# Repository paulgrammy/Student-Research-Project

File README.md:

# Student-Research-Project-
Bluetooth signal receiver with filter stage and AUX/Speaker output.

UseCase description: 

This project seeks to help students more easily understand the effects of filters on electric signals by using sound. Since Music and/or audio is composed of frequencies across a spectrum (20Hz to 20kHz), one can hear what an Low/High Pass filter would do when fed audio signals. In my Student-Research project work, I try to design a PCB that shall overline this use case.

The PCB shall process analog converted audio signal coming from a Bluetooth-capable ESP32 board. The user shall connect the board at the input and output of any given filter and shall have the option to hear the filtered and unfiltered audio signals coming out with minimal noise and distortion.

Used platforms and ICs:

- ESP32 FireBeetle board:
    https://wiki.dfrobot.com/FireBeetle_Board_ESP32_E_SKU_DFR0654
- PCM5102 DAC:
    https://www.ti.com/product/PCM5102
- MCP6001 OPAMPS:
    https://ww1.microchip.com/downloads/en/DeviceDoc/MCP6001-1R-1U-2-4-1-MHz-Low-Power-Op-Amp-DS20001733L.pdf
- TPA711 Power AMP:
    https://www.ti.com/product/TPA711

Potential software solutions for the BluetoothRx interface:

https://github.com/pschatzmann/ESP32-A2DP

https://github.com/YetAnotherElectronicsChannel/ESP32_Bluetooth_Audio_Receiver

Books and Papers:

https://web.mit.edu/6.101/www/reference/op_amps_everyone.pdf

End result:

Conclusions: 
The board works with minimal distortion up to the OpAmps single supply limits, offering almost no phase lag.
Some layout optimizations can be carried out to lower the noise floor and make implementation in the labs easier.

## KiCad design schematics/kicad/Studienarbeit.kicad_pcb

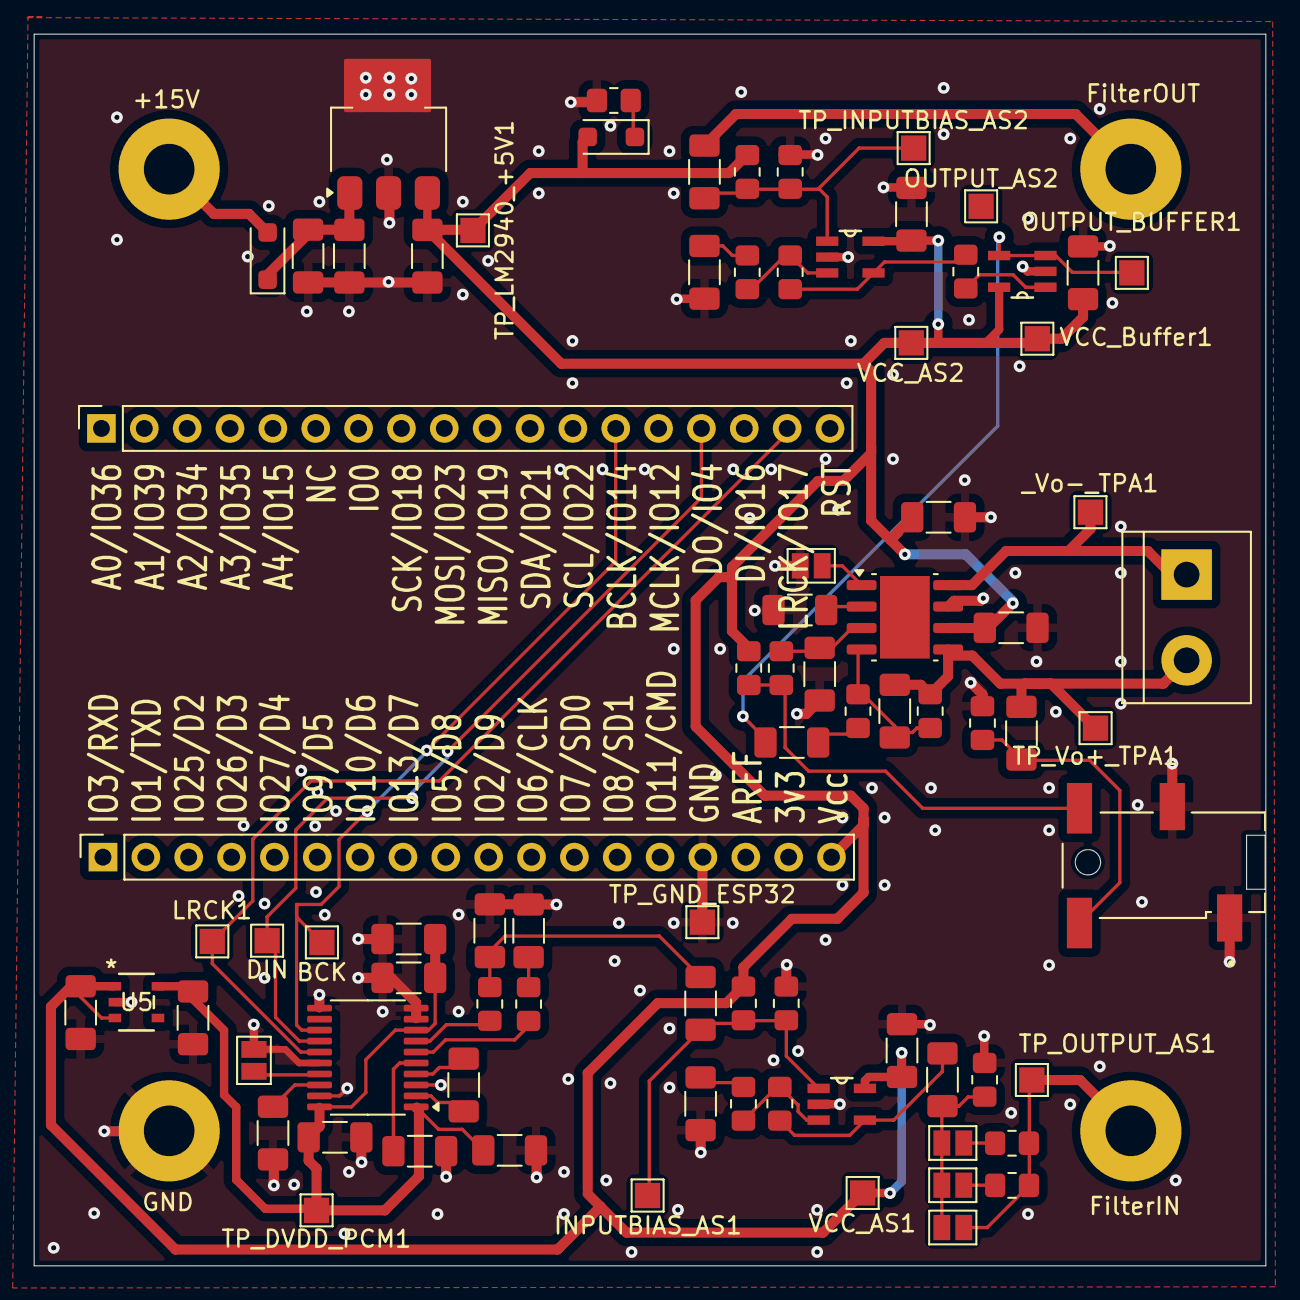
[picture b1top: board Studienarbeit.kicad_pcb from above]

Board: 2 copper layers, 73.0 x 73.0 mm, 87 parts (0 on the bottom side), 42 nets.

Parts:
BCK: TestPoint; TestPoint_Pad_1.5x1.5mm
C1_APS_PCM5102: 10uF; C_1206_3216Metric_Pad1.33x1.80mm_HandSolder
C1_CPPS_PCM1, C1_DPS_PCM1, C2_APS_PCM5102, C2_DPS_PCM1: 0.1uF; C_1206_3216Metric_Pad1.33x1.80mm_HandSolder
C2_CPPS_PCM1: 2.2uF; C_1206_3216Metric_Pad1.33x1.80mm_HandSolder
CA_PCM5102: 2.2uF; C_1206_3216Metric_Pad1.33x1.80mm_HandSolder
CB_TPA1: 2.2uF; C_1206_3216Metric_Pad1.33x1.80mm_HandSolder
CF_TPA711: 5pF; C_1206_3216Metric_Pad1.33x1.80mm_HandSolder
CG1_PCM5102, CG2_PCM5102: 2.2nF; C_1206_3216Metric_Pad1.33x1.80mm_HandSolder
CI_TPA711: 0.47uF; C_1206_3216Metric_Pad1.33x1.80mm_HandSolder
C_COUPLING_AMPSTAGE1: 10uF; C_1206_3216Metric_Pad1.33x1.80mm_HandSolder
C_COUPLING_AMPSTAGE2, C_COUPLING_AMPSTAGE3, C_COUPLING_AMPSTAGE4: 10nF; C_1206_3216Metric_Pad1.33x1.80mm_HandSolder
C_GND_AMPSTAGE1, C_GND_AMPSTAGE2, C_GND_AMPSTAGE3: 10uF; C_1206_3216Metric_Pad1.33x1.80mm_HandSolder
C_INPUT_LDO1: 0.47uF; C_1206_3216Metric_Pad1.33x1.80mm_HandSolder
C_INPUT_RT1: 22uF; C_1206_3216Metric_Pad1.33x1.80mm_HandSolder
C_INPUT_RT9080: 1uF; C_1206_3216Metric_Pad1.33x1.80mm_HandSolder
C_INPUT_TPA1, C_INPUT_TPA3: 10uF; C_1206_3216Metric_Pad1.33x1.80mm_HandSolder
C_INPUT_TPA2: 100nF; C_1206_3216Metric_Pad1.33x1.80mm_HandSolder
C_IN_+15V_1: 10uF; C_1206_3216Metric_Pad1.33x1.80mm_HandSolder
C_IN_AMPSTAGE1: 10uF; C_1206_3216Metric_Pad1.33x1.80mm_HandSolder
C_OUTPUT_LDO1: 22uF; C_1206_3216Metric_Pad1.33x1.80mm_HandSolder
C_SE/BTL_TPA1: 0.1uF; C_1206_3216Metric_Pad1.33x1.80mm_HandSolder
D1: D_Schottky; D_SOD-123F
D2: 1N4148; D_SOD-123F
DEBUG1: 0; R_0805_2012Metric_Pad1.20x1.40mm_HandSolder
DIN: TestPoint; TestPoint_Pad_1.5x1.5mm
INPUTBIAS_AS1: TestPoint; TestPoint_Pad_1.5x1.5mm
J2, J3: Conn_01x18; PinSocket_1x18_P2.54mm_Vertical
J4, J5, J6, J7: Conn_01x01_Pin; FestoBoard_Drill_Hole
J9: SJ2-35853B-SMT-TR; CUI_SJ2-35853B-SMT-TR
JP1, JP2, JP3, JP4, JP5: Jumper_2_Open; SolderJumper-2_P1.3mm_Open_Pad1.0x1.5mm
LRCK1: TestPoint; TestPoint_Pad_1.5x1.5mm
LS1: Speaker; TerminalBlock_bornier-2_P5.08mm
OUTPUT_AS2: TestPoint; TestPoint_Pad_1.5x1.5mm
OUTPUT_BUFFER1: TestPoint; TestPoint_Pad_1.5x1.5mm
R1, R2, R3, R4: 10K; R_0805_2012Metric_Pad1.20x1.40mm_HandSolder
R11: 1K; R_0805_2012Metric_Pad1.20x1.40mm_HandSolder
R12, R13: 100K; R_0805_2012Metric_Pad1.20x1.40mm_HandSolder
RF1, RF2: 5K; R_0805_2012Metric_Pad1.20x1.40mm_HandSolder
RF_TPA711: 50k; R_0805_2012Metric_Pad1.20x1.40mm_HandSolder
RG1: 100k; R_0805_2012Metric_Pad1.20x1.40mm_HandSolder
RG2: 100K; R_0805_2012Metric_Pad1.20x1.40mm_HandSolder
RI_TPA711: 10K; R_0805_2012Metric_Pad1.20x1.40mm_HandSolder
ROUTDACL1: 470; R_0805_2012Metric_Pad1.20x1.40mm_HandSolder
ROUTDACR1: 470; R_0805_2012Metric_Pad1.20x1.40mm_HandSolder
R_COUPLING_AMPSTAGE1: 100K; R_0805_2012Metric_Pad1.20x1.40mm_HandSolder
R_COUPLING_AMPSTAGE2: 10K; R_0805_2012Metric_Pad1.20x1.40mm_HandSolder
R_COUPLING_AMPSTAGE3: 1K; R_0805_2012Metric_Pad1.20x1.40mm_HandSolder
STATUS_LED1: 330; R_0805_2012Metric_Pad1.20x1.40mm_HandSolder
TP_DVDD_PCM1: TestPoint; TestPoint_Pad_1.5x1.5mm
TP_GND_ESP32: TestPoint; TestPoint_Pad_1.5x1.5mm
TP_INPUTBIAS_AS2: TestPoint; TestPoint_Pad_1.5x1.5mm
TP_LM2940_+5V1: TestPoint; TestPoint_Pad_1.5x1.5mm
TP_OUTPUT_AS1: TestPoint; TestPoint_Pad_1.5x1.5mm
TP_Vo+_TPA1: TestPoint; TestPoint_Pad_1.5x1.5mm
U1, U3, U4: MCP6001-OT; SOT95P270X145-5N
U2: PCM5102; TSSOP-20_4.4x6.5mm_P0.65mm
U5: RT9080-33GJ5; TSOT-23-5_RIT-L
U6: TPA711; Texas_R-PDSO-G8_EP2.95x4.9mm_Mask2.4x3.1mm
U7: LM2940CT-5.0; SOT-223
VCC_AS1, VCC_AS2: TestPoint; TestPoint_Pad_1.5x1.5mm
VCC_Buffer1: TestPoint; TestPoint_Pad_1.5x1.5mm
_Vo-_TPA1: TestPoint; TestPoint_Pad_1.5x1.5mm

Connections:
+3v3: C1_APS_PCM5102.1, C1_CPPS_PCM1.2, C1_DPS_PCM1.2, C2_APS_PCM5102.2, C_INPUT_RT1.2, TP_DVDD_PCM1.1, U2.1 (CPVDD), U2.8 (AVDD), U2.20 (DVDD), U5.5 (VOUT)
+5V: C_COUPLING_AMPSTAGE2.2, C_COUPLING_AMPSTAGE3.2, C_COUPLING_AMPSTAGE4.2, C_INPUT_RT9080.2, C_INPUT_TPA1.1, C_INPUT_TPA2.1, C_OUTPUT_LDO1.2, D2.2 (A), J2.18, R1.2, R3.2, R12.2, TP_LM2940_+5V1.1, U1.5 (V+), U3.5 (V+), U4.5 (V+), U5.1 (VIN), U5.3 (EN), U6.6 (V_{DD}), U7.3 (OUT), VCC_AS1.1, VCC_AS2.1, VCC_Buffer1.1
+15V: D1.2 (A), J5.1
/BCK: BCK.1, J3.13, U2.13 (BCK)
/BUFFEROUT: CI_TPA711.2, OUTPUT_BUFFER1.1, U3.3 (-), U3.4
/DIN: DIN.1, J3.15, U2.14 (DIN)
/Filter_IN: J7.1, JP3.2 (B), R_COUPLING_AMPSTAGE2.1, R_COUPLING_AMPSTAGE3.1, TP_OUTPUT_AS1.1
/Filter_OUT: C_IN_AMPSTAGE1.1, J6.1
/IN: CF_TPA711.1, RF_TPA711.2, RI_TPA711.2, U6.4 (IN)
/LDOO: C2_DPS_PCM1.1, U2.18 (LDOO)
/LRCK: J3.17, LRCK1.1, U2.15 (LRCK)
/OUTDACL: CG1_PCM5102.1, ROUTDACL1.2
/OUTDACR: CG2_PCM5102.1, C_GND_AMPSTAGE3.1, ROUTDACR1.2
/SE/~BTL_SWITCH: J9.10, R12.1, R13.1
/VNEG: C2_CPPS_PCM1.2, U2.5 (VNEG)
/Vo+: CF_TPA711.2, C_INPUT_TPA3.1, LS1.2, RF_TPA711.1, TP_Vo+_TPA1.1, U6.5 (V_{O+})
/Vo-: LS1.1, U6.8 (V_{O-}), _Vo-_TPA1.1
GND: C1_APS_PCM5102.2, C1_CPPS_PCM1.1, C1_DPS_PCM1.1, C2_APS_PCM5102.1, C2_CPPS_PCM1.1, C2_DPS_PCM1.2, CB_TPA1.2, CG1_PCM5102.2, CG2_PCM5102.2, C_COUPLING_AMPSTAGE2.1, C_COUPLING_AMPSTAGE3.1, C_COUPLING_AMPSTAGE4.1, C_GND_AMPSTAGE1.1, C_GND_AMPSTAGE2.1, C_INPUT_LDO1.1, C_INPUT_RT1.1, C_INPUT_RT9080.1, C_INPUT_TPA1.2, C_INPUT_TPA2.2, C_IN_+15V_1.2, C_OUTPUT_LDO1.1, C_SE/BTL_TPA1.2, J2.15, J4.1, J9.1, J9.3, JP4.1 (A), JP5.1 (A), R2.2, R4.2, R11.2, R_COUPLING_AMPSTAGE1.1, STATUS_LED1.1, TP_GND_ESP32.1, U1.2 (V-), U2.3 (CPGND), U2.9 (AGND), U2.10 (DEMP), U2.11 (FLT), U2.16 (FMT), U2.19 (DGND), U3.2 (V-), U4.2 (V-), U5.2 (GND), U6.7 (GND), U7.2 (GND), U7.4 (GND)
unnamed: CI_TPA711.1, RI_TPA711.1
unnamed: C_COUPLING_AMPSTAGE1.2, RF1.2, U4.4
unnamed: C_GND_AMPSTAGE1.2, RG1.1
unnamed: C_GND_AMPSTAGE2.2, RG2.1
unnamed: C_INPUT_TPA3.2, J9.2, R11.1
unnamed: C_INPUT_LDO1.2, C_IN_+15V_1.1, D1.1 (K), U7.1 (IN)
unnamed: D2.1 (K), STATUS_LED1.2
unnamed: DEBUG1.1, RF2.2, U1.4
unnamed: C_COUPLING_AMPSTAGE1.1, JP1.1 (A), JP2.1 (A), JP3.1 (A), R_COUPLING_AMPSTAGE1.2
unnamed: JP1.2 (B), R_COUPLING_AMPSTAGE2.2
unnamed: JP2.2 (B), R_COUPLING_AMPSTAGE3.2
unnamed: JP4.2 (B), U2.17 (XSMT)
unnamed: JP5.2 (B), U6.1 (SHUTDOWN)
unnamed: C_IN_AMPSTAGE1.2, R3.1, R4.1, TP_INPUTBIAS_AS2.1, U1.1 (+)
unnamed: RF2.1, RG2.2, U1.3 (-)
unnamed: CA_PCM5102.2, U2.4 (CAPM)
unnamed: CA_PCM5102.1, U2.2 (CAPP)
unnamed: ROUTDACL1.1, U2.6 (OUTL)
unnamed: ROUTDACR1.1, U2.7 (OUTR)
unnamed: DEBUG1.2, U3.1 (+)
unnamed: C_GND_AMPSTAGE3.2, INPUTBIAS_AS1.1, R1.1, R2.1, U4.1 (+)
unnamed: RF1.1, RG1.2, U4.3 (-)
unnamed: CB_TPA1.1, U6.2 (BYPASS)
unnamed: C_SE/BTL_TPA1.1, R13.2, U6.3 (SE/~BTL)

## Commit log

2024-05-15 Created first draft of block diagram.
2024-10-09 Imported LTSpice base schematic.
2024-10-09 Imported KiCAD schematics.
2024-10-09 Added Field-Notes for easy report structuring.
2024-10-09 Added notes for potential DAC PCB design.
2024-10-18 Updated LTSpice schematics.
2024-10-18 Updated Field Notes.
2024-10-18 LTSpice: Added AC-Coupling caps at output of first amp stage.
2024-10-18 KiCad: rewired PCM5120 I/O pins and dimentioned Rs and Cs
2024-10-18 KiCad: Rewired the TPA711 I/Os and dimentioned Rs and Cs
2024-10-18 KiCad: Grafics.
2024-10-18 KiCad: Added links to IC schematics.
2024-10-18 KiCad: Fixed a few ERC errors.
2024-10-18 KiCad: Dimentioned Cs.
2024-10-18 Added footprint folder for imported footprints.
2024-10-18 Added ESP32 Footprint.
2024-10-18 KiCad: Draft of PCB.
2024-10-20 KiCad: Added an LDO for stable supply voltage.
2024-10-20 LTSpice: Printed plots for report.
2024-10-20 Updated printed images.
2024-10-20 KiCad: Added test points in the schematic.
2024-10-22 Replace ESP32 Schematic with header pins.
2024-10-22 Updated schematic.
2024-10-24 Updated PCB.
2024-10-24 Added software folder.
2024-10-29 Updated the pcb schematic.
2024-10-29 Removed FIeld Notes.
2024-10-29 LTSpice: added jumper resistors for gain control.
2024-10-29 KiCad: Added jumper wires and resistors for gain control.
2024-10-29 KiCad: rerouted the jumpers.
2024-10-29 Random.
2024-11-04 Updated PCB based on feedback (1).
2024-11-07 Updated the PCB with prof feedback.
2024-11-07 Updated the parts list.
2024-11-07 Added screenshots of simulation.
2024-11-13 Added schematic screenshots.
2024-11-13 Updated the audio jack to a switching jack.
2024-11-13 Rezolved Jack footprint issue.
2024-11-13 Updated design.
2024-11-17 Updated interface with changes from Prof.
2024-11-20 Last board updates before ordering.
2025-01-16 Updated MCP footprint and symbol
2025-01-16 Re-Added copper Layer
2025-01-16 Updated output pins of the ESP
2025-01-19 Replaced footprint with the one from the prof.
2025-01-19 Temp
